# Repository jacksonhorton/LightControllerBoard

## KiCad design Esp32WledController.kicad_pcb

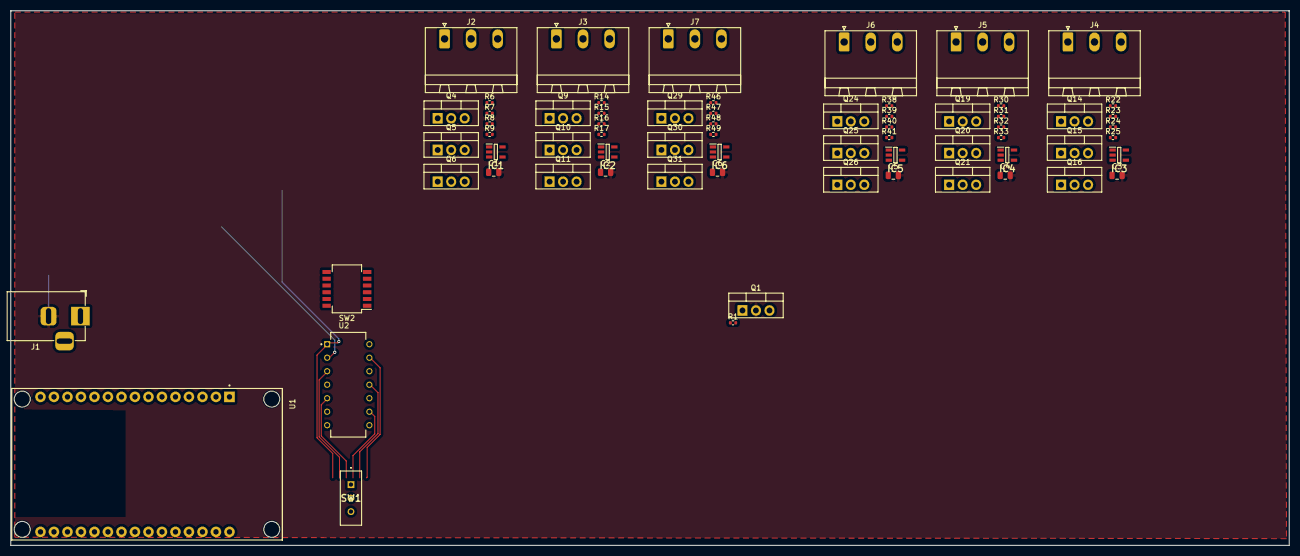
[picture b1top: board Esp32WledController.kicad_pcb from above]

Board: 2 copper layers, 240.5 x 100.6 mm, 67 parts (0 on the bottom side), 52 nets.

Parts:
C1, C2, C3, C4, C5, C6: 0.1µ; C_0805_2012Metric
IC1, IC2, IC3, IC4, IC5, IC6: SN74LV1T34DBVR; SOT95P280X145-5N
J1: Conn_01x02; BarrelJack_Horizontal
J2: Output 1; PhoenixContact_MSTBA_2,5_3-G_1x03_P5.00mm_Horizontal
J3: Output 2; PhoenixContact_MSTBA_2,5_3-G_1x03_P5.00mm_Horizontal
J4: Output 3; PhoenixContact_MSTBA_2,5_3-G_1x03_P5.00mm_Horizontal
J5: Output 4; PhoenixContact_MSTBA_2,5_3-G_1x03_P5.00mm_Horizontal
J6: Output 5; PhoenixContact_MSTBA_2,5_3-G_1x03_P5.00mm_Horizontal
J7: Output 6; PhoenixContact_MSTBA_2,5_3-G_1x03_P5.00mm_Horizontal
Q1, Q4, Q5, Q6, Q9, Q10, Q11, Q14, Q15, Q16, Q19, Q20, Q21, Q24, Q25, Q26, Q29, Q30, Q31: FQP27P06; TO-220-3_Vertical
R1: 10kΩ; R_0402_1005Metric
R6, R7, R8, R14, R15, R16, R22, R23, R24, R30, R31, R32, R38, R39, R40, R46, R47, R48: 10k; R_0402_1005Metric
R9, R17, R25, R33, R41, R49: 100; R_0402_1005Metric
SW1: SW_SPDT; SS12SDP2
SW2: SW_DIP_x06; SW_DIP_SPSTx06_Slide_Copal_CHS-06B_W7.62mm_P1.27mm
U1: ESP32-DEVKIT-V1; MODULE_ESP32_DEVKIT_V1
U2: SN7404N

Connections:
/6-light-outputs/Data1_OUT: Q6.3 (S), R8.1
/6-light-outputs/Data2_OUT: Q11.3 (S), R16.1
/6-light-outputs/Data3_OUT: Q16.3 (S), R24.1
/6-light-outputs/Data4_OUT: Q21.3 (S), R32.1
/6-light-outputs/Data5_OUT: Q26.3 (S), R40.1
/6-light-outputs/Data6_OUT: Q31.3 (S), R48.1
/6-light-outputs/Output 1/Data_OUT: IC1.4 (Y), J2.2
/6-light-outputs/Output 2/Data_OUT: IC2.4 (Y), J3.2
/6-light-outputs/Output 3/Data_OUT: IC3.4 (Y), J4.2
/6-light-outputs/Output 4/Data_OUT: IC4.4 (Y), J5.2
/6-light-outputs/Output 5/Data_OUT: IC5.4 (Y), J6.2
/6-light-outputs/Output 6/Data_OUT: IC6.4 (Y), J7.2
/6-light-outputs/Signal_1: Q4.1 (G), R6.2, SW2.12, U2.1 (1A)
/6-light-outputs/Signal_1_INV: Q5.1 (G), R7.2, U2.2 (1Y)
/6-light-outputs/Signal_2: Q9.1 (G), R14.2, SW2.11, U2.3 (2A)
/6-light-outputs/Signal_2_INV: Q10.1 (G), R15.2, U2.4 (2Y)
/6-light-outputs/Signal_3: Q14.1 (G), R22.2, SW2.10, U2.5 (3A)
/6-light-outputs/Signal_3_INV: Q15.1 (G), R23.2, U2.6 (3Y)
/6-light-outputs/Signal_4: Q19.1 (G), R30.2, SW2.9, U2.9 (4A)
/6-light-outputs/Signal_4_INV: Q20.1 (G), R31.2, U2.8 (4Y)
/6-light-outputs/Signal_5: Q24.1 (G), R38.2, SW2.8, U2.11 (5A)
/6-light-outputs/Signal_5_INV: Q25.1 (G), R39.2, U2.10 (5Y)
/6-light-outputs/Signal_6: Q29.1 (G), R46.2, SW2.7, U2.13 (6A)
/6-light-outputs/Signal_6_INV: Q30.1 (G), R47.2, U2.12 (6Y)
GND: IC1.3 (GND), IC2.3 (GND), IC3.3 (GND), IC4.3 (GND), IC5.3 (GND), IC6.3 (GND), J1.1, J2.3, J3.3, J4.3, J5.3, J6.3, J7.3, SW1.2 (B), U1.2 (GND), U1.29 (GND), U2.7 (GND)
unnamed: IC1.2 (A), Q4.2 (D)
unnamed: C1.1, IC1.5 (VCC)
unnamed: IC2.2 (A), Q9.2 (D)
unnamed: C2.1, IC2.5 (VCC)
unnamed: IC3.2 (A), Q14.2 (D)
unnamed: C3.1, IC3.5 (VCC)
unnamed: IC4.2 (A), Q19.2 (D)
unnamed: C4.1, IC4.5 (VCC)
unnamed: IC5.2 (A), Q24.2 (D)
unnamed: C5.1, IC5.5 (VCC)
unnamed: IC6.2 (A), Q29.2 (D)
unnamed: C6.1, IC6.5 (VCC)
unnamed: Q1.1 (G), R1.1, SW1.3 (C)
unnamed: Q5.2 (D), Q6.1 (G), R8.2
unnamed: Q6.2 (D), R9.2
unnamed: Q10.2 (D), Q11.1 (G), R16.2
unnamed: Q11.2 (D), R17.2
unnamed: Q15.2 (D), Q16.1 (G), R24.2
unnamed: Q16.2 (D), R25.2
unnamed: Q20.2 (D), Q21.1 (G), R32.2
unnamed: Q21.2 (D), R33.2
unnamed: Q25.2 (D), Q26.1 (G), R40.2
unnamed: Q26.2 (D), R41.2
unnamed: Q30.2 (D), Q31.1 (G), R48.2
unnamed: Q31.2 (D), R49.2
VBUS: Q1.3 (S), Q4.3 (S), Q5.3 (S), Q9.3 (S), Q10.3 (S), Q14.3 (S), Q15.3 (S), Q19.3 (S), Q20.3 (S), Q24.3 (S), Q25.3 (S), Q29.3 (S), Q30.3 (S), R1.2, R6.1, R7.1, R14.1, R15.1, R22.1, R23.1, R30.1, R31.1, R38.1, R39.1, R46.1, R47.1, SW2.1, SW2.2, SW2.3, SW2.4, SW2.5, SW2.6, U1.17 (VP), U2.14 (VCC)
VCC: C1.2, C2.2, C3.2, C4.2, C5.2, C6.2, J1.2, Q1.2 (D)

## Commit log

2024-12-09 Initial commit.
2024-12-09 Closed files in lock files. Added archive
